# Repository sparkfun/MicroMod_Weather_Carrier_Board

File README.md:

SparkFun MicroMod Weather Carrier Board
========================================

[*SparkFun MicroMod Weather Carrier Board (SEN-16794)*](https://www.sparkfun.com/products/16794)

The MicroMod Weather Carrier Board for the [SparkFun MicroMod Ecosystem](https://www.sparkfun.com/micromod) allows you to create your own weather station with one of a multitude of processors. The carrier board includes three sensors: the BME280 temperature, pressure and humidity sensor, the VEML6075 UV sensor and the AS3935 Lightning detector. There is also a 3-pin latch terminal to add an external [soil moisture sensor](https://www.sparkfun.com/products/13637), a pair RJ11 jacks to plug in the wind and rain sensors included with our [Weather Meter Kit](https://www.sparkfun.com/products/15901) as well as a microSD card slot so you can plug in an SD card to log the weather data.

Repository Contents
-------------------

* **/Documentation** - Data sheets, additional product information 
* **/Hardware** - Eagle design files (.brd, .sch)
* **/Production** - Production panel files (.brd)
* **/Examples** - Arduino examples for the MicroMod Weather Carrier Board

Documentation
--------------
* **Libraries** - Arduino libraries required for the MicroMod Weather Carrier Board.
   * **[BME280 Library](https://github.com/sparkfun/SparkFun_BME280_Arduino_Library)** - Arduino Library for the BME280.
   * **[VEML6075 Library](https://github.com/sparkfun/SparkFun_VEML6075_Arduino_Library)** - Arduino library for the VEML6075.
   * **[AS3935 Library](https://github.com/sparkfun/SparkFun_AS3935_Lightning_Detector_Arduino_Library)** - Arduino library for the AS3935.
* **[Hookup Guide](https://learn.sparkfun.com/tutorials/micromod-weather-carrier-board-hookup-guide)** - Basic hookup guide for the MicroMod Weather Carrier Board.
* **[SparkFun Fritzing repo](https://github.com/sparkfun/Fritzing_Parts)** - Fritzing diagrams for SparkFun products.
* **[SparkFun 3D Model repo](https://github.com/sparkfun/3D_Models)** - 3D models of SparkFun products. 
* **[SparkFun Graphical Datasheets](https://github.com/sparkfun/Graphical_Datasheets)** -Graphical Datasheets for various SparkFun products.

Product Versions
----------------
* [SEN-16794](https://www.sparkfun.com/products/16794)- Initial release of the MicroMod Weather Carrier Board.

License Information
-------------------

This product is _**open source**_! 

Please review the LICENSE.md file for license information. 

If you have any questions or concerns on licensing, please contact technical support on our [SparkFun forums](https://forum.sparkfun.com/viewforum.php?f=152).

Distributed as-is; no warranty is given.

- Your friends at SparkFun.

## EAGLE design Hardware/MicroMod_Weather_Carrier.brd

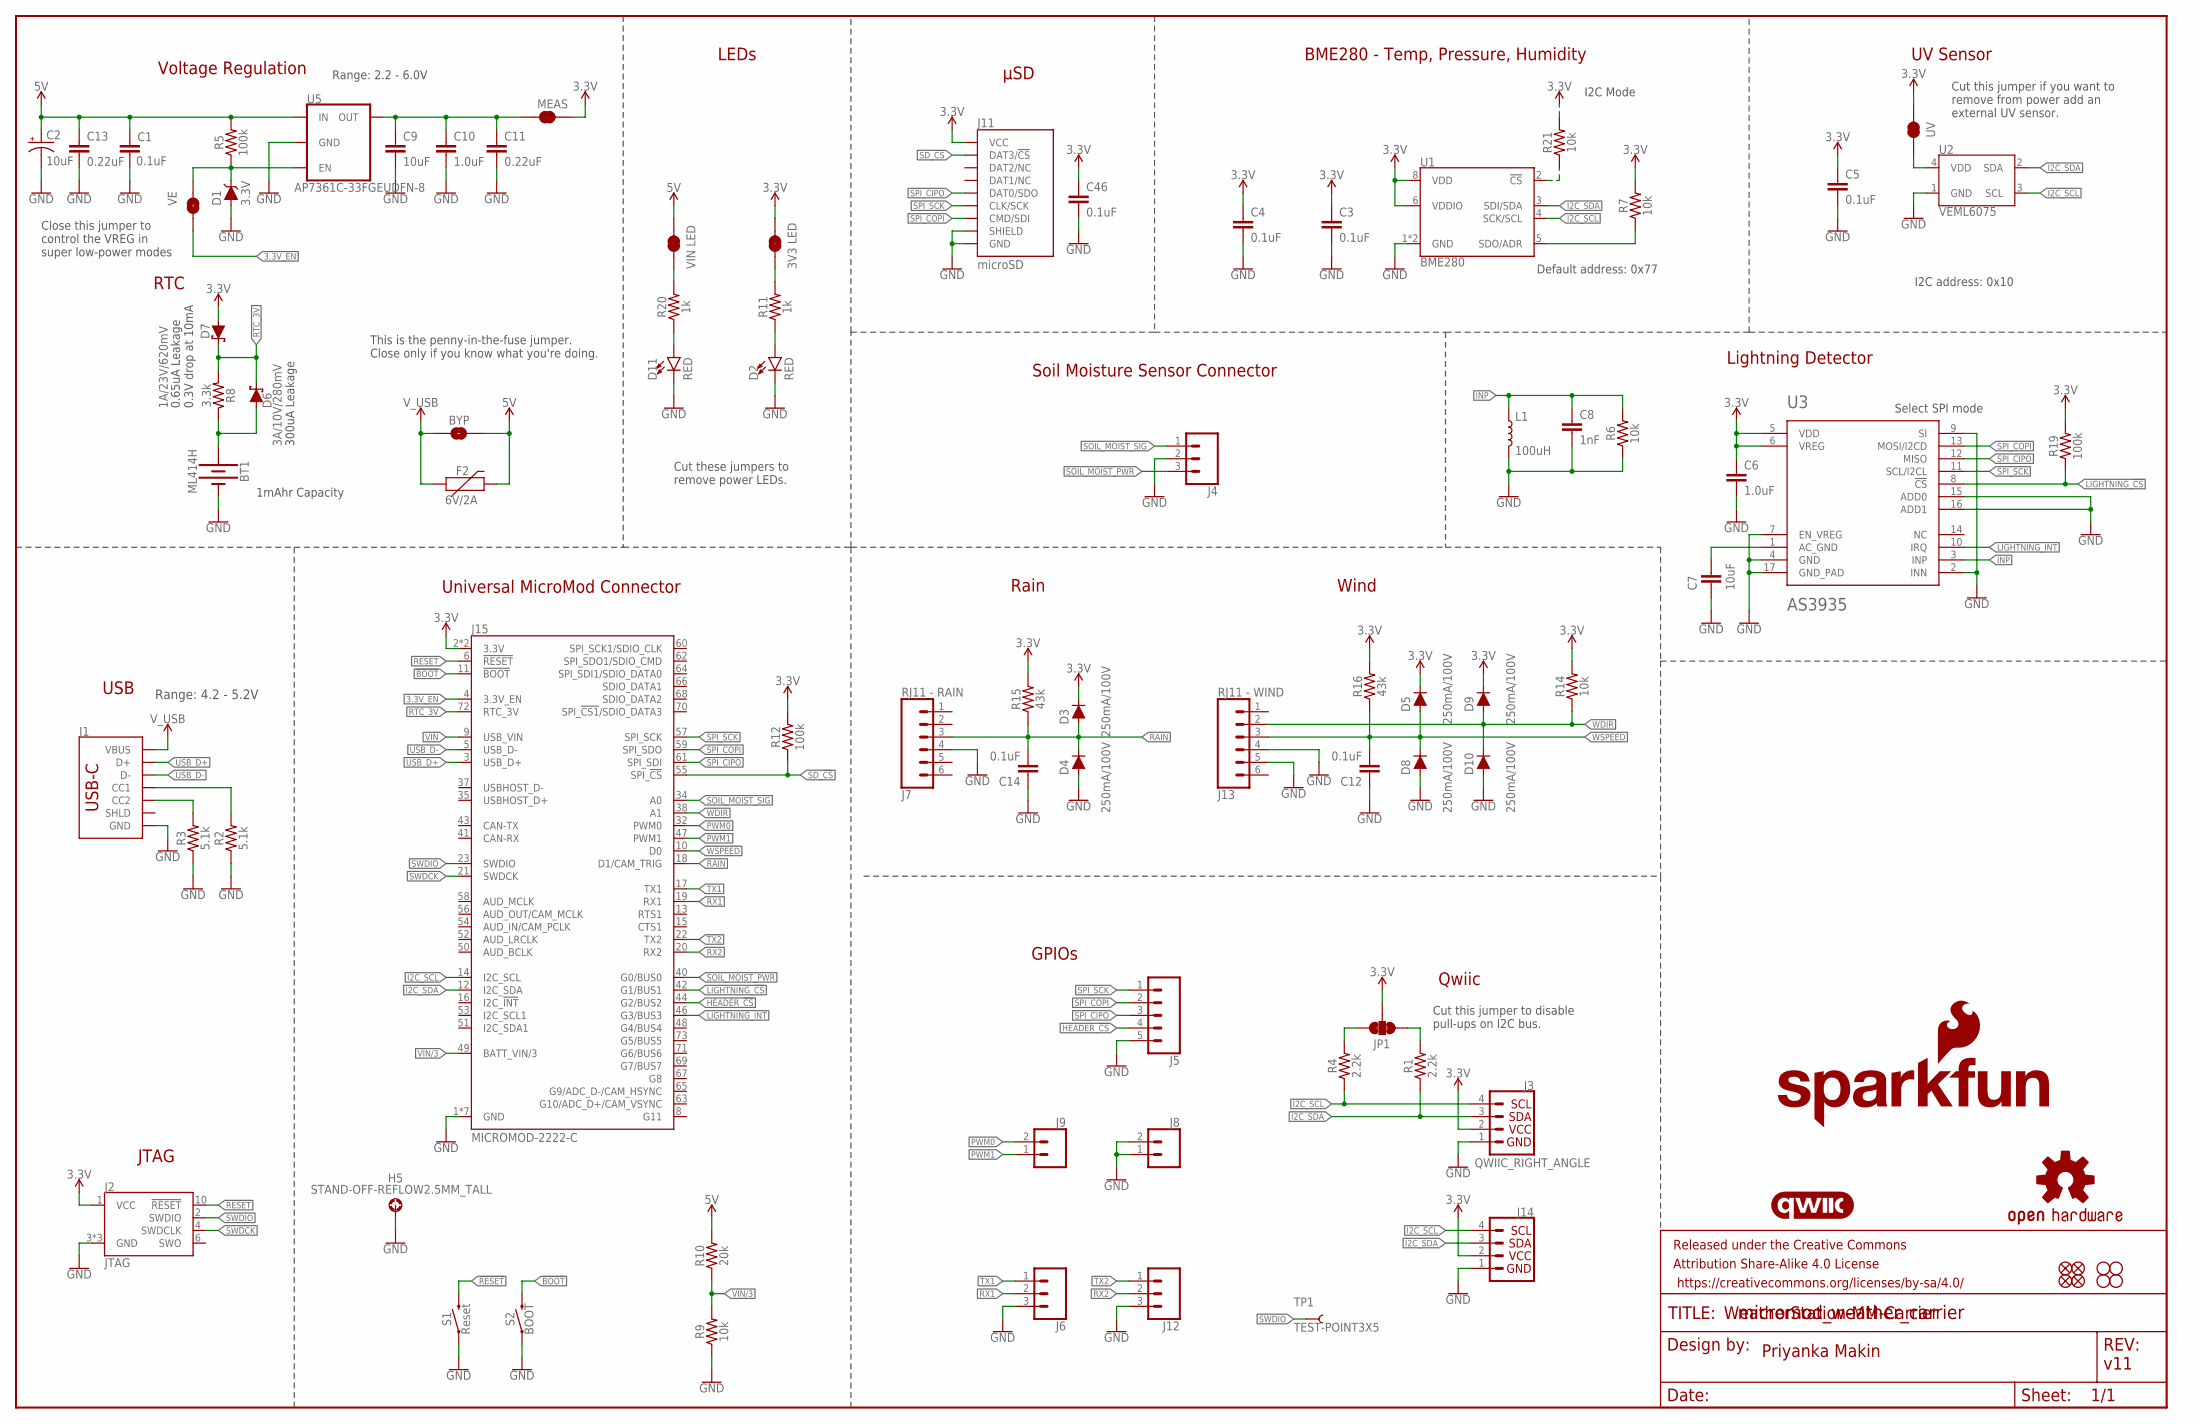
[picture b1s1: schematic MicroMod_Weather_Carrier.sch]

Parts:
BT1: ML414H; ML414H_IV01E
BYP: JUMPER-SMT_2_NO_SILK; SMT-JUMPER_2_NO_SILK
C1, C3, C4, C5, C12, C14, C46: 0.1uF; 0603
C2: 10uF; EIA3216
C6, C10: 1.0uF; 0603
C7, C9: 10uF; 0603
C8: 1nF; 0603
C11, C13: 0.22uF; 0603
D1: 3.3V; SOD-323
D2, D11: RED; LED-0603
D3, D4, D5, D8, D9, D10: 250mA/100V; SOD-323
D6: 3A/10V/280mV; SOD-323
D7: 1A/23V/620mV; SOD-323
F2: 6V/2A; 1210
FD1, FD2, FD3, FD4: FIDUCIALUFIDUCIAL; FIDUCIAL-MICRO
FRAME1: FRAME-LEDGER; CREATIVE_COMMONS
H1, H2, H3, H4: STAND-OFF
H5: STAND-OFF-REFLOW2.5MM_TALL; STAND-OFF-REFLOW-M2.5
J1: USB_C_2-LAYER_PADS; USB-C-16P-2LAYER-PADS
J2: JTAG; 2X5-PTH-1.27MM
J3: QWIIC_RIGHT_ANGLE; JST04_1MM_RA
J4: CONN_03LATCH; LATCHTERMINAL-5MM-3
J5: CONN_05NO_SILK; 1X05_NO_SILK
J6, J12: CONN_031X03_NO_SILK; 1X03_NO_SILK
J7: RJ11 - RAIN; RJ11-6
J8, J9: CONN_021X02_NO_SILK; 1X02_NO_SILK
J11: microSD; MICRO-SD-SOCKET
J13: RJ11 - WIND; RJ11-6
J14: I2C_STANDARD_NO_SILK; 1X04_NO_SILK
J15: MICROMOD-2222-C; M.2-CONNECTOR-E
JP1: JUMPER-SMT_3_2-NC_TRACE_SILK; SMT-JUMPER_3_2-NC_TRACE_SILK
JP2: VIN LED; SMT-JUMPER_2_NC_TRACE_SILK
JP3: UV; SMT-JUMPER_2_NC_TRACE_SILK
JP4: 3V3 LED; SMT-JUMPER_2_NC_TRACE_SILK
JP6: VE; SMT-JUMPER_2_NO_SILK
L1: 100uH; MA5532-AE
LOGO1: SFE_LOGO_NAME_FLAME.2_INCH; SFE_LOGO_NAME_FLAME_.2
LOGO2: QWIIC_LOGO_CONNECTOR; QWIIC_5.5MM
LOGO3: OSHW-LOGOM; OSHW-LOGO-M
MEAS: JUMPER-COMBO_2_NC_TRACE; COMBO-JUMPER_2_NC_TRACE
R1, R4: 2.2k; 0603
R2, R3: 5.1k; 0603
R5, R12, R19: 100k; 0603
R6, R7, R9, R14, R21: 10k; 0603
R8: 3.3k; 0603
R10: 20k; 0603
R11, R20: 1k; 0603
R15, R16: 43k; 0603
S1: Reset; TACTILE_SWITCH_SMD_5.2MM
S2: BOOT; TACTILE_SWITCH_SMD_5.2MM
TP1: TEST-POINT3X5; PAD.03X.05
U1: BME280; LGA-8-2.5X2.5
U2: VEML6075; VEML6075_A3OP
U3: AS3935; 16LD_MLPQ
U5: AP7361C-33FGEUDFN-8; UDFN-8

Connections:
3.3V: C3.1, C4.1, C5.1, C6.1, C46.1, D3.C, D5.C, D7.A, D9.C, J2.1 (VCC), J3.2, J11.VCC, J14.2, J15.2 (3.3V), J15.74 (3.3V), JP1.2, JP3.2, JP4.2, MEAS.2, MEAS.4 (2), R7.2, R12.2, R14.2, R15.2, R16.2, R19.2, R21.2, U1.6 (VDDIO), U1.8 (VDD), U3.5 (VDD), U3.6 (VREG)
3.3V_EN: J15.4 (3.3V_EN), JP6.1
!BOOT!: J15.11 (!BOOT!), S2.3 (2), S2.4 (2)
!RESET!: J2.10 (!RESET), J15.6 (!RESET!), S1.3 (2), S1.4 (2)
GND: BT1.-, C1.2, C2.-, C3.2, C4.2, C5.2, C6.2, C7.2, C8.2, C9.2, C10.2, C11.2, C12.1, C13.2, C14.1, C46.2, D1.A, D2.C, D4.A, D8.A, D10.A, D11.C, H5.1, J1.GND, J1.GND2 (GND), J2.3 (GND), J2.5 (GND), J2.9 (GND), J3.1, J4.2, J5.5, J6.3, J7.4, J8.1, J8.2, J11.CD1 (SHIELD), J11.GND, J11.GND1 (GND), J11.GND3 (GND), J12.3, J13.4, J13.5, J14.1, J15.1 (GND), J15.7 (GND), J15.33 (GND), J15.36 (GND), J15.39 (GND), J15.45 (GND), J15.75 (GND), L1.2, R2.1, R3.1, R6.1, R9.1, S1.1, S1.2 (1), S2.1, S2.2 (1), U1.1 (GND), U1.7 (GND), U2.1 (GND), U3.2 (INN), U3.4 (GND), U3.7 (EN_VREG), U3.9 (SI), U3.15 (ADD0), U3.16 (ADD1), U3.17 (GND_PAD), U5.4 (GND), U5.EP (GND)
HEADER_!CS!: J5.4, J15.44 (G2/BUS2)
I2C_SCL: J3.4, J14.4, J15.14 (I2C_SCL), R4.1, U1.4 (SCK/SCL), U2.3 (SCL)
I2C_SDA: J3.3, J14.3, J15.12 (I2C_SDA), R1.1, U1.3 (SDI/SDA), U2.2 (SDA)
INP: C8.1, L1.1, R6.2, U3.3 (INP)
LIGHTNING_!CS!: J15.42 (G1/BUS1), R19.1, U3.8 (!CS)
LIGHTNING_INT: J15.46 (G3/BUS3), U3.10 (IRQ)
unnamed: C9.1, C10.1, C11.1, MEAS.1, MEAS.3 (1), U5.1 (OUT)
unnamed: JP1.3, R4.2
unnamed: JP1.1, R1.2
unnamed: JP4.1, R11.2
unnamed: JP2.1, R20.2
unnamed: D2.A, R11.1
unnamed: JP3.1, U2.4 (VDD)
unnamed: R7.1, U1.5 (SDO/ADR)
unnamed: J1.A5 (CC1), R2.2
unnamed: J1.B5 (CC2), R3.2
unnamed: BT1.+, D6.A, R8.1
unnamed: C7.1, U3.1 (AC_GND)
unnamed: D11.A, R20.1
unnamed: R21.1, U1.2 (!CS)
PWM0: J9.2, J15.32 (PWM0)
PWM1: J9.1, J15.47 (PWM1)
RAIN: C14.2, D3.A, D4.C, J7.3, J15.18 (D1/CAM_TRIG), R15.1
RTC_3V: D6.C, D7.C, J15.72 (RTC_3V), R8.2
RX1: J6.2, J15.19 (RX1)
RX2: J12.2, J15.20 (RX2)
SD_!CS!: J11.CS/DAT3 (DAT3/!CS!), J15.55 (SPI_!CS!), R12.1
SOIL_MOIST_PWR: J4.3, J15.40 (G0/BUS0)
SOIL_MOIST_SIG: J4.1, J15.34 (A0)
SPI_CIPO: J5.3, J11.DO/DAT0 (DAT0/SDO), J15.61 (SPI_SDI), U3.12 (MISO)
SPI_COPI: J5.2, J11.DI/CMD (CMD/SDI), J15.59 (SPI_SDO), U3.13 (MOSI/I2CD)
SPI_SCK: J5.1, J11.SCLK (CLK/SCK), J15.57 (SPI_SCK), U3.11 (SCL/I2CL)
SWDCK: J2.4 (SWDCLK), J15.21 (SWDCK)
SWDIO: J2.2 (SWDIO), J15.23 (SWDIO), TP1.P$1
TX1: J6.1, J15.17 (TX1)
TX2: J12.1, J15.22 (TX2)
USB_D+: J1.A6 (D+), J1.B6 (D+), J15.3 (USB_D+)
USB_D-: J1.A7 (D-), J1.B7 (D-), J15.5 (USB_D-)
VIN: BYP.2, C1.1, C2.+, C13.1, F2.2, J15.9 (USB_VIN), JP2.2, R5.2, R10.2, U5.8 (IN)
VIN/3: J15.49 (BATT_VIN/3), R9.2, R10.1
VREG_EN: D1.C, JP6.2, R5.1, U5.5 (EN)
V_USB: BYP.1, F2.1, J1.VBUS1 (VBUS), J1.VBUS2 (VBUS)
WDIR: D9.A, D10.C, J13.2, J15.38 (A1), R14.1
WSPEED: C12.2, D5.A, D8.C, J13.3, J15.10 (D0), R16.1

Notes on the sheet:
300uA Leakage
0.65uA Leakage 0.3V drop at 10mA
1mAhr Capacity
This is the penny-in-the-fuse jumper. Close only if you know what you're doing.
JTAG
USB
GPIOs
Qwiic
RTC
Voltage Regulation
Universal MicroMod Connector
Priyanka Makin
WeatherStation-MM-Carrier
BME280 - Temp, Pressure, Humidity
UV Sensor
Soil Moisture Sensor Connector
Rain
Wind
LEDs
Lightning Detector
I2C Mode
Default address: 0x77
I2C address: 0x10
Select SPI mode
v11
Cut this jumper if you want to remove from power add an external UV sensor.
Cut this jumper to disable pull-ups on I2C bus.
Cut these jumpers to remove power LEDs.
μSD
Range: 4.2 - 5.2V
Range: 2.2 - 6.0V
Close this jumper to control the VREG in super low-power modes

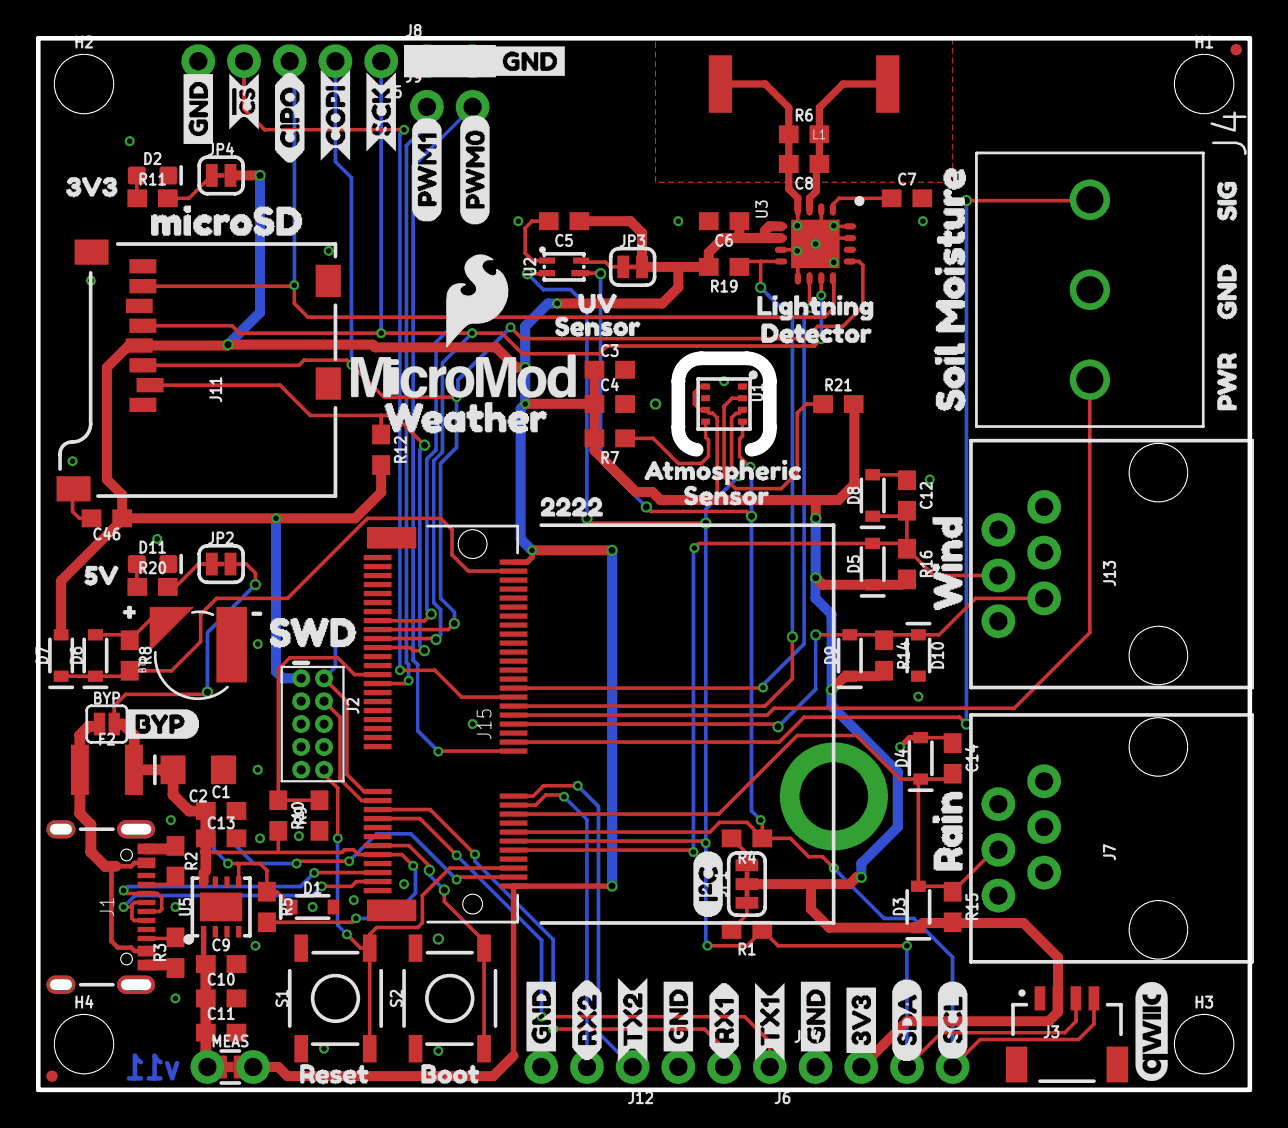
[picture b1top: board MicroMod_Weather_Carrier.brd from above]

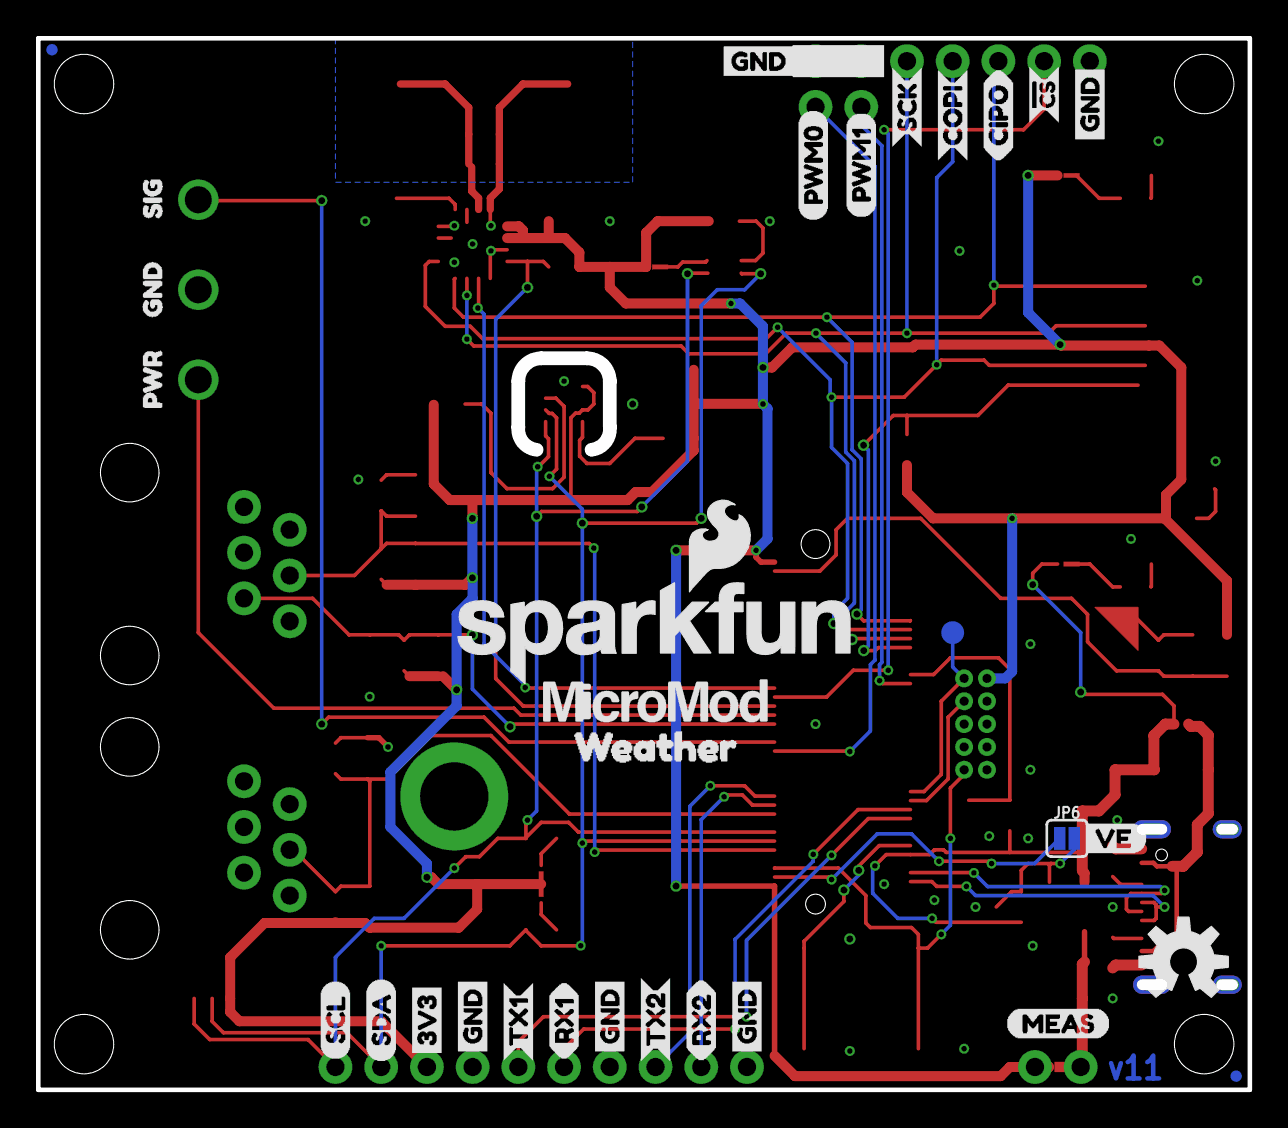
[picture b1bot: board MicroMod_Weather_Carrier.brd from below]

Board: 2 copper layers, 67.3 x 58.4 mm, 157 parts (31 on the bottom side), 49 nets.

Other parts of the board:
U$1: 3V31
U$2: RESET3
U$3: RAIN1
U$4, U$57: GND0
U$5: MEAS
U$6, U$11, U$23, U$32, U$33, U$36, U$42, U$45, U$53, U$54: GND_P
U$7, U$8: COPI0
U$9, U$49: SCK_O
U$10, U$52: !CS_O
U$12, U$24: PWR2
U$13, U$63: SIG1
U$14: BYP0
U$15, U$61: PWM10
U$16, U$58: WEATHER4
U$17, U$30: RX25
U$18: 5V0
U$19: BOOT2
U$20: ATMOSPHERIC0
U$21: VE0
U$22: LIGHTNING8
U$25, U$29: RX10
U$27, U$50: CIPO0
U$28, U$56: TX24
U$31, U$41: TX13
U$34: SENSOR7
U$35: MICROSD0
U$37: I2C
U$38, U$46: 3V3_P
U$39, U$47: SDA_IO
U$40, U$48: SCL_IO
U$43: SWD1
U$44: SFE_LOGO_FLAME_.2
U$55: 22229
U$59, U$60: PWM01
U$62: UV6
U$64: SENSOR1
U$65: SOIL_MOISTURE2
U$66: WIND0
U$67, U$68: MICROMOD_LOGO_.5
U$69: #0
U$70: #1
U$71: DETECTOR2

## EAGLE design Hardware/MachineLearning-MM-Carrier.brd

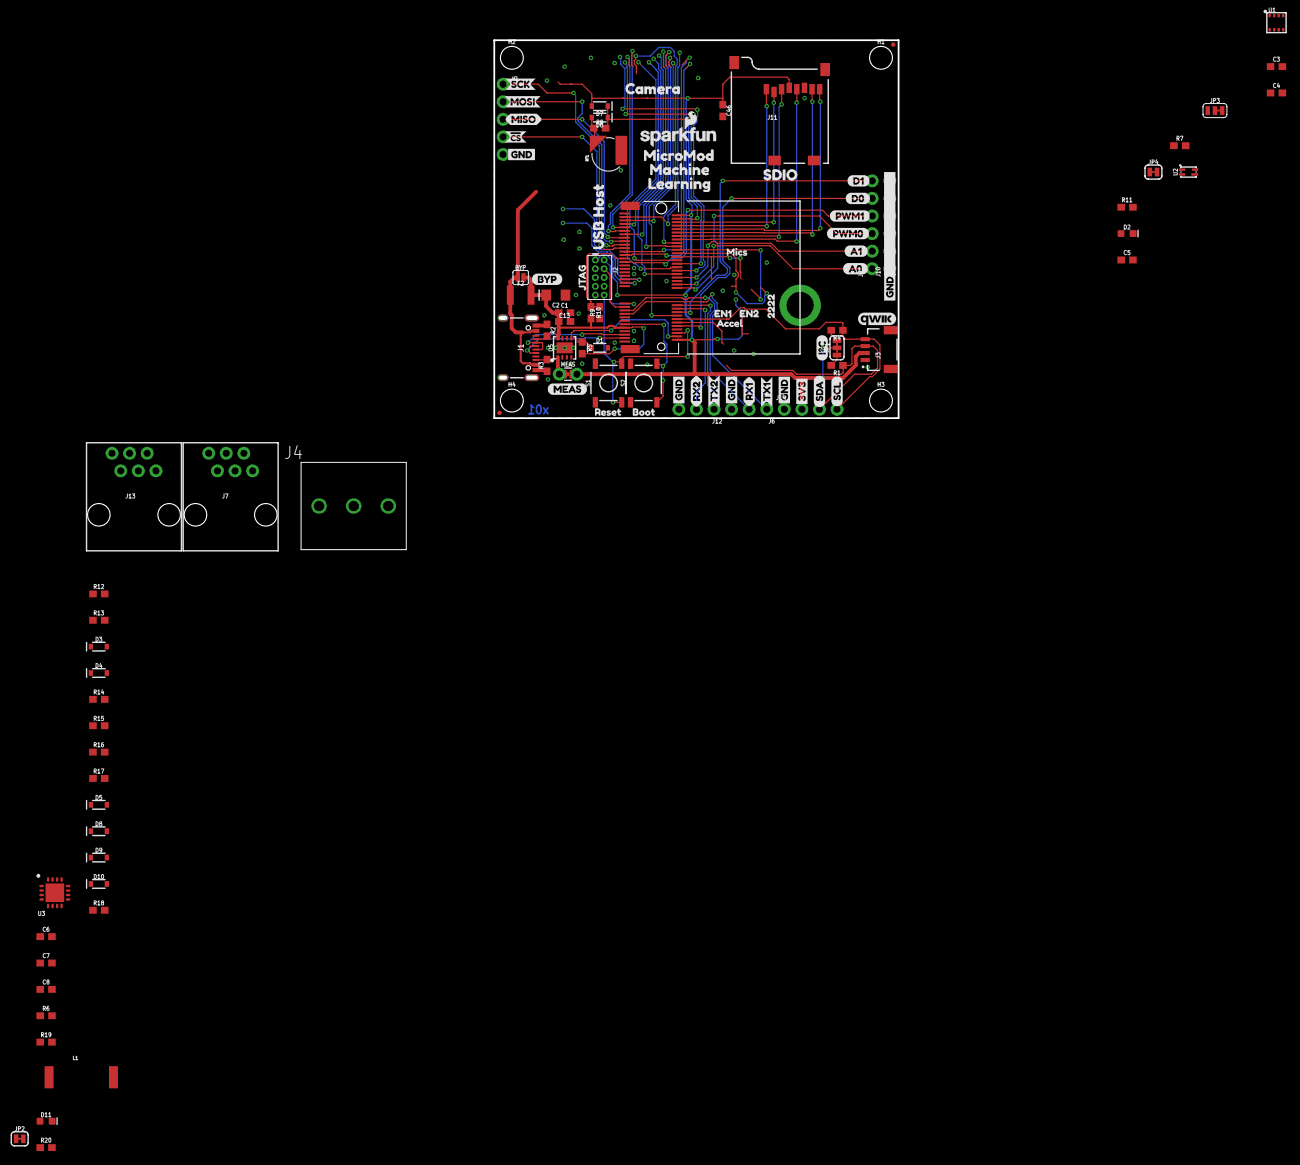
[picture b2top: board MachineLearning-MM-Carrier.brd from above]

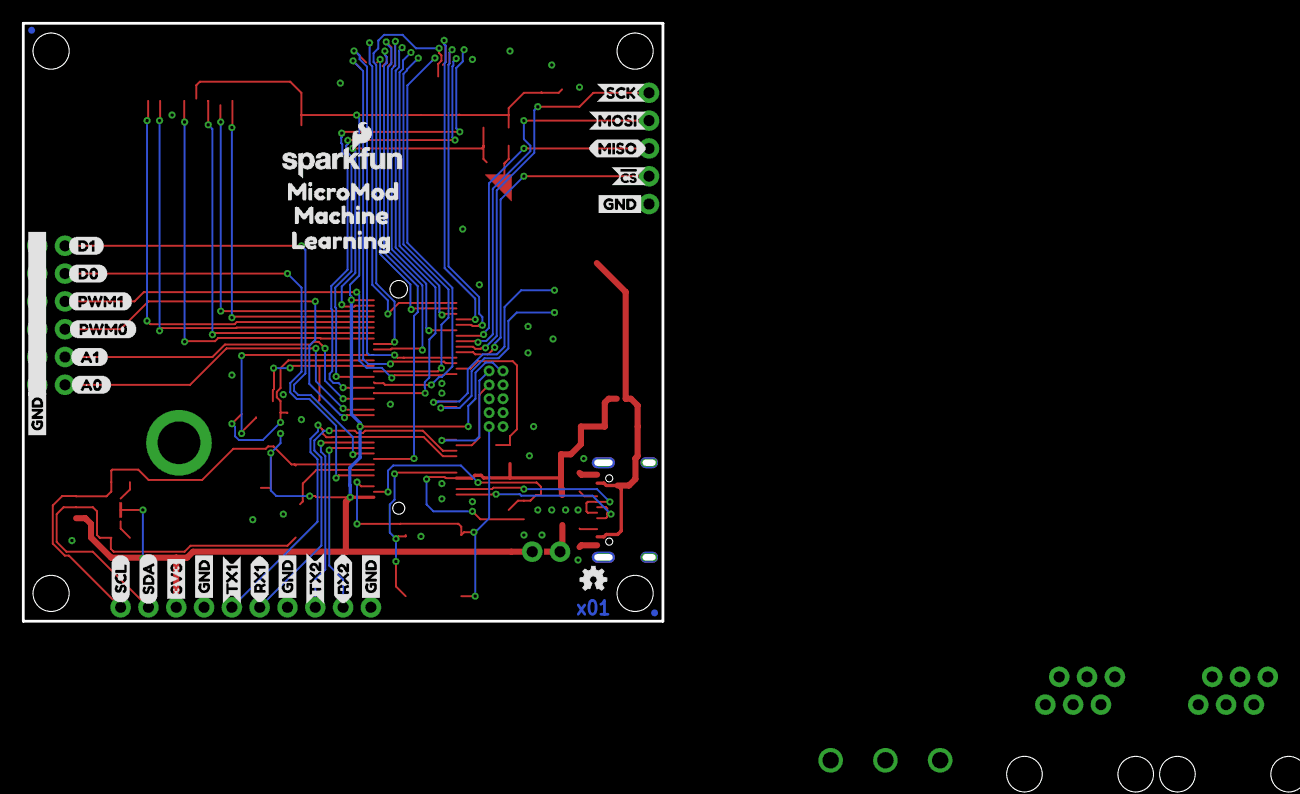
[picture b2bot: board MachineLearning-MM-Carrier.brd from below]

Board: 2 copper layers, 58.4 x 54.6 mm, 148 parts (29 on the bottom side), 59 nets.

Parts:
BT1: ML414H; ML414H_IV01E
BYP: JUMPER-SMT_2_NO_SILK; SMT-JUMPER_2_NO_SILK
C1, C3, C4, C5, C46: 0.1uF; 0603
C2: 10uF; EIA3216
C6: 1.0uF; 0603
C7: 10uF; 0603
C8: 1nF; 0603
C13: 0.22uF; 0603
D1: 3.3V; SOD-323
D2: RED; LED-0603
D3, D4, D5, D8, D9, D10: 250mA/100V; SOD-323
D6: 3A/10V/280mV; SOD-323
D7: 1A/23V/620mV; SOD-323
D11: Yellow; LED-0603
F2: 6V/2A; 1210
FD1, FD2, FD3, FD4: FIDUCIALUFIDUCIAL; FIDUCIAL-MICRO
FRAME1: FRAME-LEDGER; CREATIVE_COMMONS
H1, H2, H3, H4: STAND-OFF
H5: STAND-OFF-REFLOW2.5MM_TALL; STAND-OFF-REFLOW-M2.5
J1: USB-C-16P-2LAYER-PADS
J2: JTAG; 2X5-PTH-1.27MM
J3: QWIIC_RIGHT_ANGLE; JST04_1MM_RA
J4: LATCHTERMINAL-5MM-3
J5: 1X05_NO_SILK
J6, J12: 1X03_NO_SILK
J7: RJ11 - RAIN; RJ11-6
J8, J10: 1X06_NO_SILK
J9: MICROMOD-2222-C; M.2-CONNECTOR-E
J11: microSD; MICRO-SD-SOCKET
J13: RJ11 - WIND; RJ11-6
J14: 1X04_NO_SILK
JP1: SMT-JUMPER_3_2-NC_TRACE_SILK
JP2: VIN LED ENABLE; SMT-JUMPER_2_NC_TRACE_SILK
JP3: EN ADR PU; SMT-JUMPER_3_1-NC_TRACE_SILK
JP4: 3V3 LED ENABLE; SMT-JUMPER_2_NC_TRACE_SILK
L1: 100uH; MA5532-AE
LOGO1, LOGO4: SFE_LOGO_NAME_FLAME.1_INCH; SFE_LOGO_NAME_FLAME_.1
LOGO2: QWIIC_LOGO_CONNECTOR; QWIIC_5.5MM
LOGO3: OSHW-LOGOMINI; OSHW-LOGO-MINI
MEAS: COMBO-JUMPER_2_NC_TRACE
R1, R4: 2.2k; 0603
R2, R3: 5.1k; 0603
R5: 100k; 0603
R6, R9, R19: 10k; 0603
R7, R18: 4.7k; 0603
R8, R11, R12, R13, R14, R15, R16, R17, R20: 1k; 0603
R10: 20k; 0603
S1: Reset; TACTILE_SWITCH_SMD_5.2MM
S2: BOOT; TACTILE_SWITCH_SMD_5.2MM
U1: BME280; LGA-8-2.5X2.5
U2: VEML6075; VEML6075_A3OP
U3: AS3935; 16LD_MLPQ
U5: AP7361C-33FGE; 8-UDFN
U$1: ACCEL6
U$2: RESET3
U$3: CAMERA5
U$4, U$66: LEARNING3
U$5: MEAS
U$6, U$11, U$23, U$32, U$33, U$36, U$42, U$45, U$53, U$54: GND_P
U$7, U$50: MOSI_O
U$8, U$51: MISO_I
U$9, U$49: SCK_O
U$10, U$52: !CS_O
U$12, U$13: D13
U$14, U$16: D02
U$15, U$61: PWM10
U$17, U$30: RX25
U$18: JTAG_TO
U$19: BOOT2
U$20: USB_HOST0
U$21: SDIO1
U$22, U$65: MACHINE2
U$24, U$64: MICROMOD0
U$25, U$29: RX10
U$26: MICS0
U$27: BYP
U$28, U$56: TX24
U$31, U$41: TX13
U$34: EN13
U$35: EN24
U$37: I2C
U$38, U$46: 3V3_P
U$39, U$47: SDA_IO
U$40, U$48: SCL_IO
U$43, U$44: A00
U$55: 22229
U$57, U$58: A10
U$59, U$60: PWM01

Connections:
3.3V: C3.1, C4.1, C5.1, C6.1, C46.1, D7.A, J2.1, J3.2, J4.1, J9.2, J9.74, J11.VCC, J14.2, JP1.2, JP4.2, MEAS.2, MEAS.4, R7.2, R19.2, U1.2, U1.6, U1.8, U2.4, U3.5, U3.6
3.3V_EN: D1.C, J9.4, R5.1, U5.5
5V: D3.C, D9.C, D10.C, R18.2
!BOOT!: J9.11, S2.3, S2.4
!RESET!: J2.10, J9.6, S1.3, S1.4
A0: J8.1, J9.34
A1: J8.2, J9.38
BME_ADR: JP3.2, U1.5
D0: J8.5, J9.10
D1: J8.6, J9.18
GND: BT1.-, C1.2, C2.-, C3.2, C4.2, C5.2, C6.2, C7.2, C8.2, C13.2, C46.2, D1.A, D2.C, D4.A, D5.A, D8.A, D11.C, H5.1, J1.GND, J1.GND2, J2.3, J2.5, J2.9, J3.1, J4.2, J5.5, J6.3, J9.1, J9.7, J9.33, J9.36, J9.39, J9.45, J9.75, J10.1, J10.2, J10.3, J10.4, J10.5, J10.6, J11.CD1, J11.GND, J11.GND1, J11.GND3, J12.3, J14.1, JP3.1, L1.2, R2.1, R3.1, R6.1, R9.1, R12.1, R14.2, R15.2, S1.1, S1.2, S2.1, S2.2, U1.1, U1.7, U2.1, U3.2, U3.4, U3.7, U3.9, U3.17, U5.4, U5.EP
I2C_SCL: J3.4, J9.14, J14.4, R4.1, U1.4, U2.3
I2C_SDA: J3.3, J9.12, J14.3, R1.1, U1.3, U2.2
INP: C8.1, L1.1, R6.2, U3.3
unnamed: MEAS.1, MEAS.3, U5.1
unnamed: JP1.3, R4.2
unnamed: JP1.1, R1.2
unnamed: JP4.1, R11.2
unnamed: JP2.1, R20.2
unnamed: D2.A, R11.1
unnamed: J7.4, R12.2
unnamed: JP3.3, R7.1
unnamed: J7.3, R13.2
unnamed: J1.A5, R2.2
unnamed: J1.B5, R3.2
unnamed: J13.5, R14.1
unnamed: J13.4, R15.1
unnamed: BT1.+, D6.A, R8.1
unnamed: C7.1, U3.1
unnamed: D11.A, R20.1
unnamed: J13.3, R16.1
unnamed: J13.2, R17.1
PWM0: J8.3, J9.32
PWM1: J8.4, J9.47
RAIN: D3.A, D4.C, R13.1
RTC_3V: D6.C, D7.C, J9.72, R8.2
RX1: J6.2, J9.19
RX2: J9.20, J12.2
SD_CLK: J9.60, J11.SCLK
SD_CMD: J9.62, J11.DI
SD_DAT0: J9.64, J11.DO
SD_DAT1: J9.66, J11.RSV2
SD_DAT2: J9.68, J11.RSV1
SD_DAT3: J9.70, J11.CS
SPI_!CS!: J5.4, J9.55, R19.1, U3.8
SPI_CLK: J5.1, J9.57, U3.11
SPI_MISO: J5.3, J9.61, U3.12
SPI_MOSI: J5.2, J9.59, U3.13
SWDCK: J2.4, J9.21
SWDIO: J2.2, J9.23
TX1: J6.1, J9.17
TX2: J9.22, J12.1
USB_D+: J1.A6, J1.B6, J9.3
USB_D-: J1.A7, J1.B7, J9.5
VIN: BYP.2, C1.1, C2.+, C13.1, F2.2, J9.9, JP2.2, R5.2, R10.2, U5.8
VIN/3: J9.49, R9.2, R10.1
V_USB: BYP.1, F2.1, J1.VBUS1, J1.VBUS2
WDIR: D5.C, D9.A, R17.2, R18.1
WSPEED: D8.C, D10.A, R16.2

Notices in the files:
parts and their libraries:
SparkFun-Aesthetics: Licensing: Creative Commons ShareAlike 4.0 International - https://creativecommons.org/licenses/by-sa/4.0
SparkFun-Aesthetics: Released under the Creative Commons Attribution Share-Alike 4.0 License
SparkFun-Aesthetics: https://creativecommons.org/licenses/by-sa/4.0
